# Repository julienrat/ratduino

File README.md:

Moduluino
======================================

Le moduluino est un arduino basé sur l'ATmega328P, il a l'avantage de concentrer le minimum pour fonctionner. son utilisation est destinée aux modules d'exposition,
le cout estimé est de 13 euros TTC chez seeedstudio.

Les fichiers de production ainsi que la BOM sont disposibles  et sont destinés à etre utilisés avec les services seeedstudio prototyping
http://www.seeedstudio.com/service/index.php?r=site/pcbService&type=pcba

Les fichiers sources sont compatibles EAGLE avec la librairie Open Parts Library  (http://www.seeedstudio.com/wiki/Open_parts_library)
Licence GNU GPL

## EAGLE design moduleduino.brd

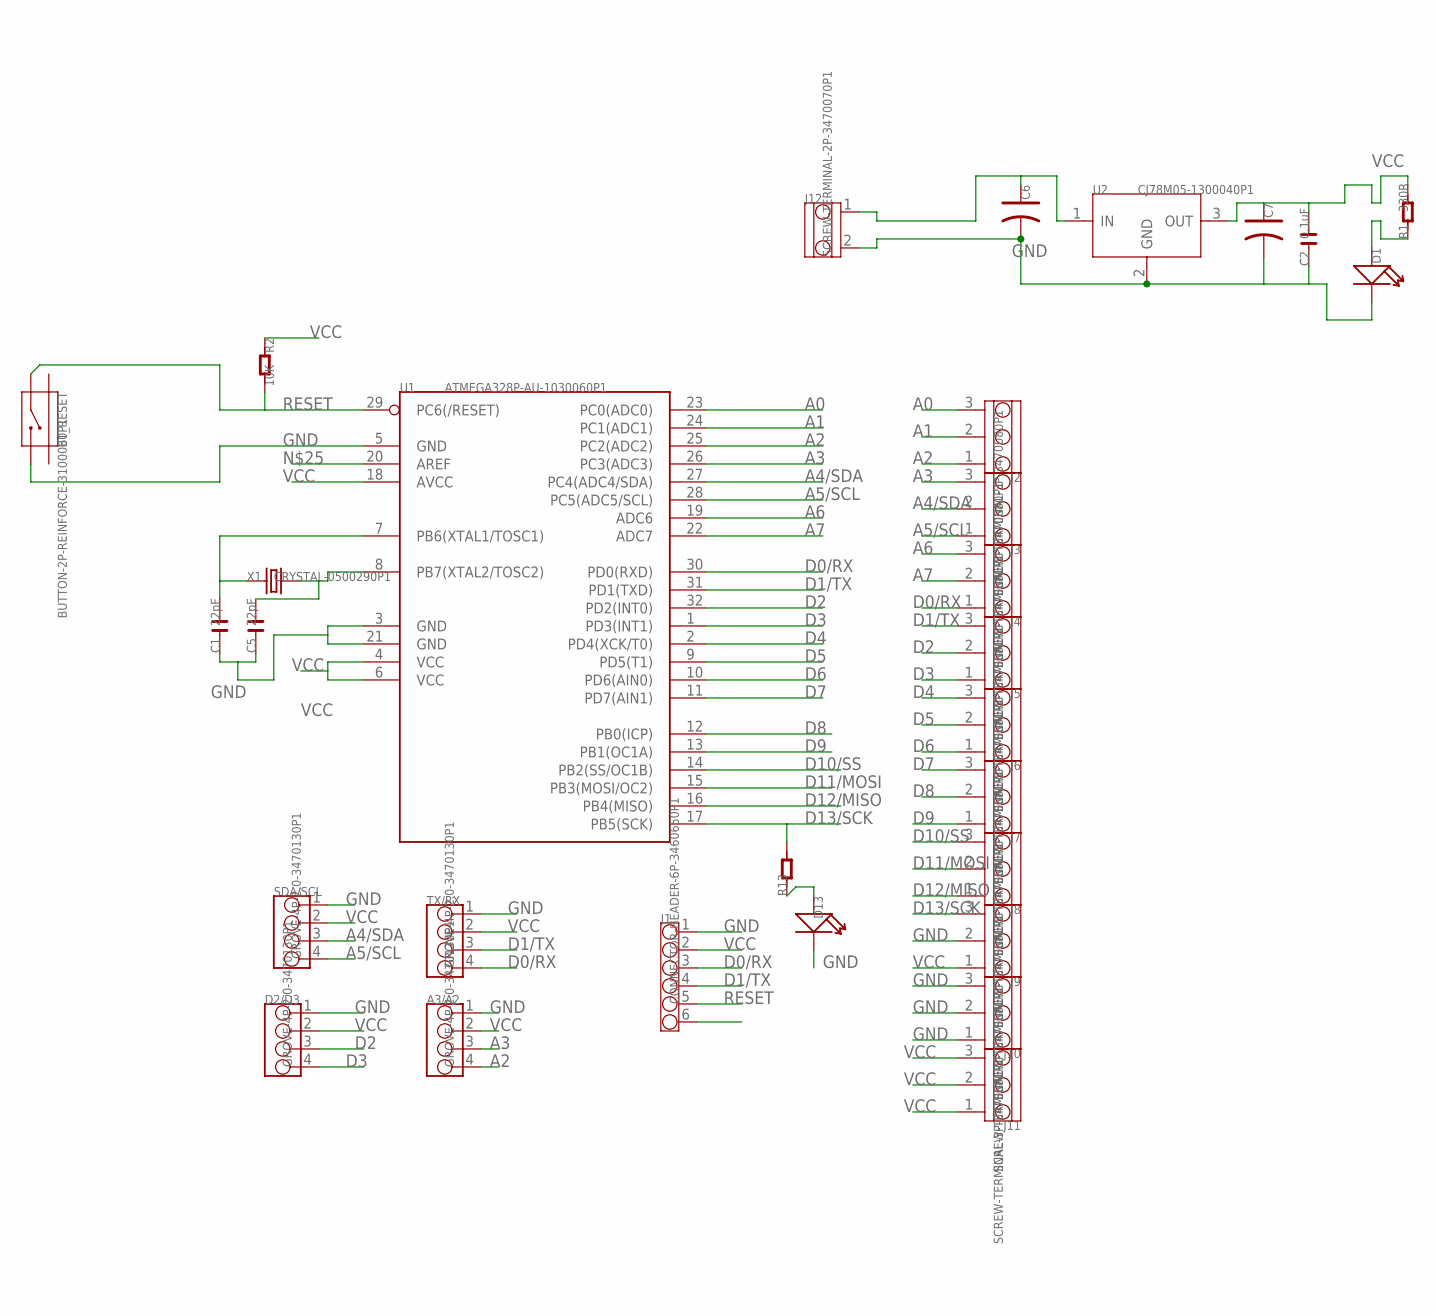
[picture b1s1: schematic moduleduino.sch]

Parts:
A3/A2: GROVE-4P-2.0-3470130P1; 4P-2.0
BT_RESET: BUTTON-2P-REINFORCE-3100060P1; 4P-SMD-7.0X3.5X3.5H-90D
C1, C5: 22pF; C0603
C2: 0.1uF; C0603
C6, C7: C-POLAR-B; AVX-B
D1, D13: LED; LED0603
D2/D3: GROVE-4P-2.0-3470130P1; 4P-2.0
J1: CONNECTOR-HEADER-6P-3460650P1; 1X6P-2.54-2.54-11.6-3.0-BLACK-MALE
J2, J3, J4, J5, J6, J7, J8, J9, J10, J11: SCREW-TERMINAL-3P-3470080P1; 3P-5.0
J12: SCREW-TERMINAL-2P-3470070P1; 2P-3.5
R1: 330R; R0603
R2: 10K; R0603
R13: R-0603; R0603
SDA/SCL: GROVE-4P-2.0-3470130P1; 4P-2.0
TX/RX: GROVE-4P-2.0-3470130P1; 4P-2.0
U1: ATMEGA328P-AU-1030060P1; TQFP32
U2: CJ78M05-1300040P1; TO252
X1: CRYSTAL-0500290P1; 2P-SMD-5.0X3.2

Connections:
A0: J2.3, U1.23 (PC0(ADC0))
A1: J2.2, U1.24 (PC1(ADC1))
A2: A3/A2.4, J2.1, U1.25 (PC2(ADC2))
A3: A3/A2.3, J3.3, U1.26 (PC3(ADC3))
A4/SDA: J3.2, SDA/SCL.3, U1.27 (PC4(ADC4/SDA))
A5/SCL: J3.1, SDA/SCL.4, U1.28 (PC5(ADC5/SCL))
A6: J4.3, U1.19 (ADC6)
A7: J4.2, U1.22 (ADC7)
D0/RX: J1.3, J4.1, TX/RX.4, U1.30 (PD0(RXD))
D1/TX: J1.4, J5.3, TX/RX.3, U1.31 (PD1(TXD))
D2: D2/D3.3, J5.2, U1.32 (PD2(INT0))
D3: D2/D3.4, J5.1, U1.1 (PD3(INT1))
D4: J6.3, U1.2 (PD4(XCK/T0))
D5: J6.2, U1.9 (PD5(T1))
D6: J6.1, U1.10 (PD6(AIN0))
D7: J7.3, U1.11 (PD7(AIN1))
D8: J7.2, U1.12 (PB0(ICP))
D9: J7.1, U1.13 (PB1(OC1A))
D10/SS: J8.3, U1.14 (PB2(SS/OC1B))
D11/MOSI: J8.2, U1.15 (PB3(MOSI/OC2))
D12/MISO: J8.1, U1.16 (PB4(MISO))
D13/SCK: J9.3, R13.2, U1.17 (PB5(SCK))
GND: A3/A2.1, BT_RESET.2, C1.1, C2.1, C5.1, C6.- (2), C7.- (2), D1.-, D2/D3.1, D13.-, J1.1, J9.2, J10.1, J10.2, J10.3, J12.2, SDA/SCL.1, TX/RX.1, U1.3 (GND), U1.5 (GND), U1.21 (GND), U2.2 (GND)
unnamed: D13.+, R13.1
unnamed: C1.2, U1.7 (PB6(XTAL1/TOSC1)), X1.1
unnamed: C5.2, U1.8 (PB7(XTAL2/TOSC2)), X1.2
unnamed: C6.+ (1), J12.1, U2.1 (IN)
unnamed: D1.+, R1.1
RESET: BT_RESET.1, J1.5, R2.2, U1.29 (PC6(/RESET))
VCC: A3/A2.2, C2.2, C7.+ (1), D2/D3.2, J1.2, J9.1, J11.1, J11.2, J11.3, R1.2, R2.1, SDA/SCL.2, TX/RX.2, U1.4 (VCC), U1.6 (VCC), U1.18 (AVCC), U2.3 (OUT)

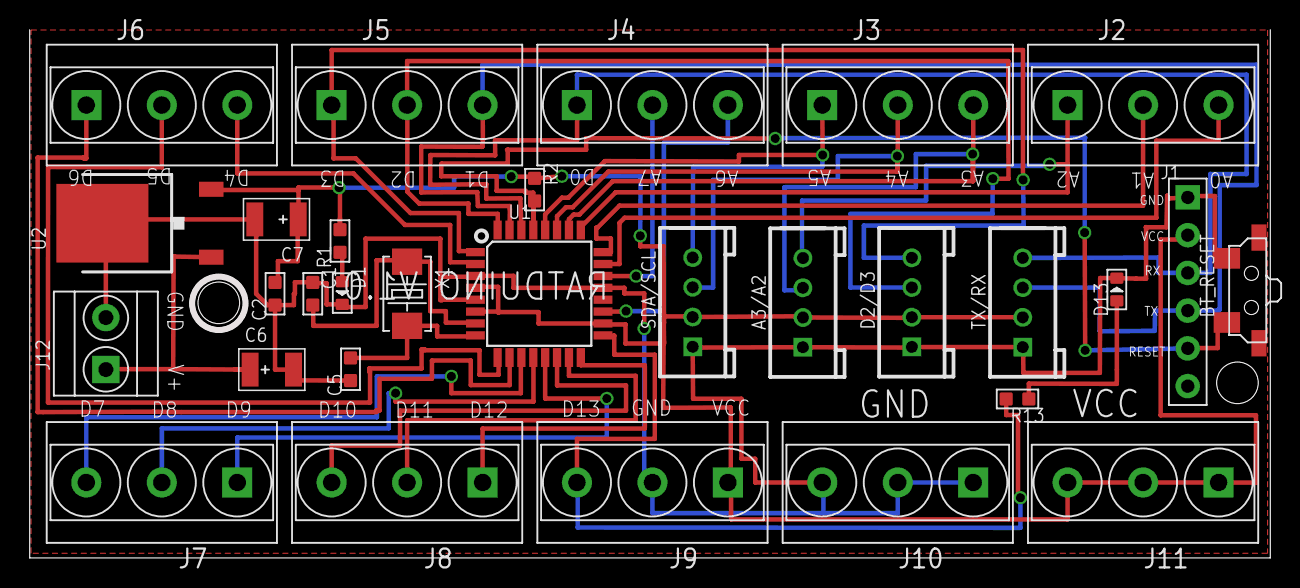
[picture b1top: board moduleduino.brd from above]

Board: 4 copper layers, 83.1 x 35.1 mm, 30 parts (0 on the bottom side), 30 nets.

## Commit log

2013-12-18 ajout du projet ratduino
2014-03-20 + ‘.sparkleshare’
